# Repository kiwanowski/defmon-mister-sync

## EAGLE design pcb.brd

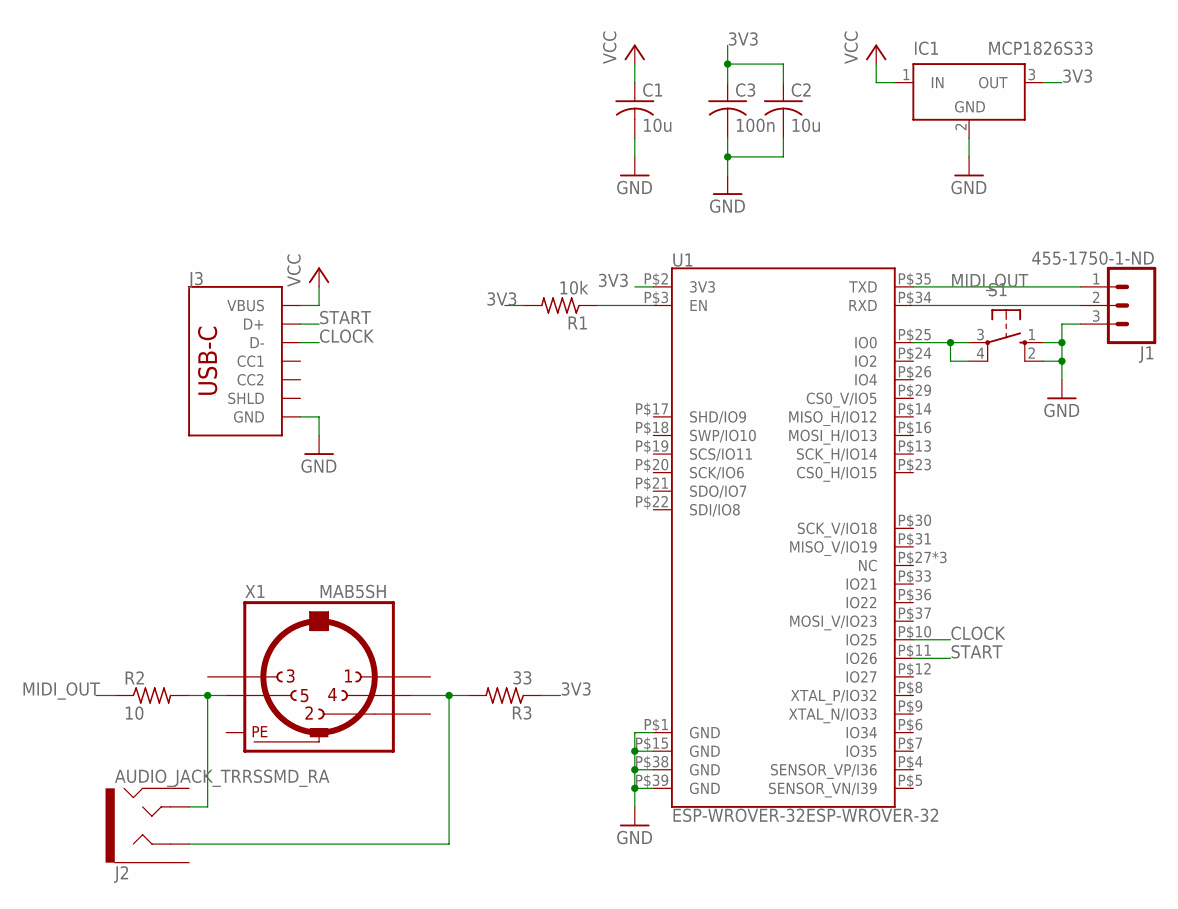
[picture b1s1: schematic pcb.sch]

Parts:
C1, C2: 10u; C0805
C3: 100n; C0805
IC1: MCP1826S33; SOT223
J1: 455-1750-1-ND; 1X03
J2: AUDIO_JACK_TRRSSMD_RA; AUDIO_JACK_3.5MM_TRRS_SMD_RA
J3: USB_C_2-LAYER_PADS; USB-C-16P-2LAYER-PADS
R1: 10k; R0805
R2: 10; R0805
R3: 33; R0805
S1: 10-XX; B3F-10XX
U1: ESP-WROVER-32ESP-WROVER-32; ESP-WROVER-32
X1: MAB5SH

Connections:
3V3: C2.1, C3.1, IC1.3 (OUT), R1.2, R3.1, U1.P$2 (3V3)
CLOCK: J3.A7 (D-), J3.B7 (D-), U1.P$10 (IO25)
GND: C1.2, C2.2, C3.2, IC1.2 (GND), IC1.4 (GND), J1.3, J3.GND, J3.GND2 (GND), S1.1 (S), S1.2 (S1), U1.P$1 (GND), U1.P$15 (GND), U1.P$38 (GND), U1.P$39 (GND)
MIDI_OUT: J1.1, R2.1, U1.P$35 (TXD)
unnamed: J2.RING1, R3.2, X1.4
unnamed: R1.1, U1.P$3 (EN)
unnamed: J2.TIP, R2.2, X1.5
unnamed: J1.2, U1.P$34 (RXD)
unnamed: S1.3, S1.4 (P1), U1.P$25 (IO0)
PE: X1.PE, X1.PE@ (PE)
START: J3.A6 (D+), J3.B6 (D+), U1.P$11 (IO26)
VCC: C1.1, IC1.1 (IN), J3.VBUS1 (VBUS), J3.VBUS2 (VBUS)

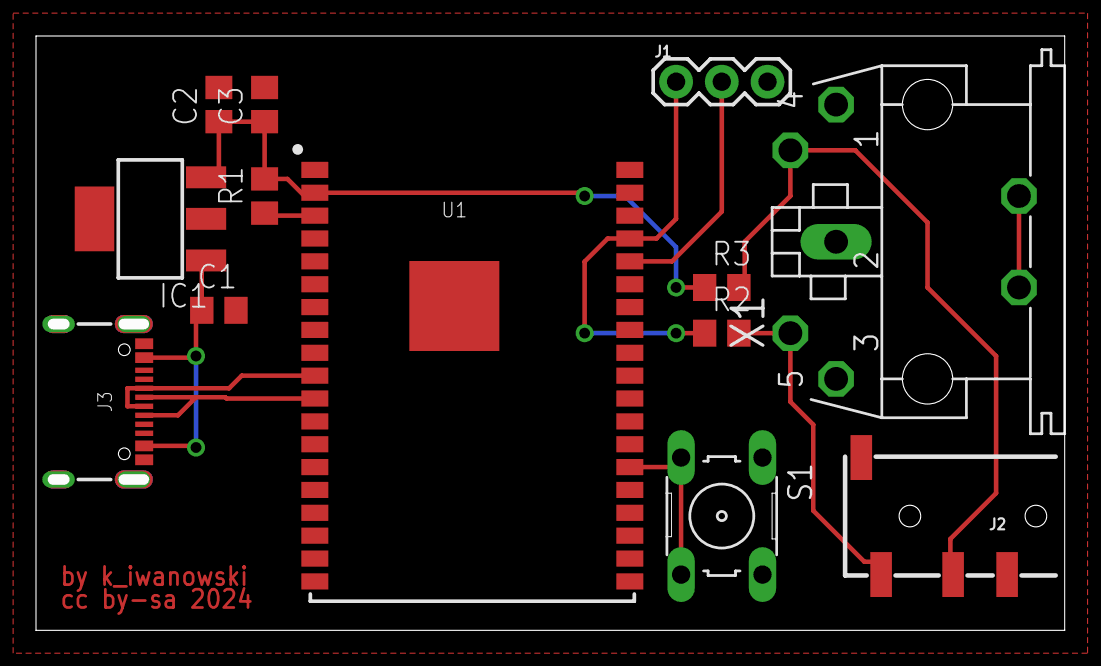
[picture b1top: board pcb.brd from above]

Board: 2 copper layers, 56.6 x 32.4 mm, 13 parts (0 on the bottom side), 12 nets.

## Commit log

2024-04-09 initial
2024-04-10 Added schematics
2024-04-28 small fixes

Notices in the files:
pcb.brd:
cc by-sa 2024
parts and their libraries:
SparkFun-Connectors: Licensing: Creative Commons ShareAlike 4.0 International - https://creativecommons.org/licenses/by-sa/4.0
